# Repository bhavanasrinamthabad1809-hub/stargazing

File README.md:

#  Stargazing

**A panda-shaped task clock that nags me when it's time to start, yells when time's up, and gives me a star if I actually did the thing.**

## Why I made this

I am a professional procrastinator.

I don't mean "oh, I put things off a little." I mean I sit down to read a book for 30 minutes, and somehow it is two hours later and I have watched a video about how bridges are built. Phone alarms don't work on me, because I swipe them away without even waking up properly. To-do apps don't work either, because opening an app is already a task I'm avoiding.

So I asked myself: what if the thing that nags me was a *physical object* that sits on my desk, can't be swiped away, and is kind of cute so I don't hate it?

That's Stargazing. Every task has a **start time** and a **deadline**. At the start time it beeps at me. At the deadline it sounds an alarm. In between, I either press **DONE** and get a star in my little night sky, or I press **NOT DONE** and get nothing. It turns out I will do a surprising amount of work for a tiny pixel star.

---

## What it does

- Shows the **time and date** like a normal desk clock.
- Holds up to **10 tasks**, each with a name, a start time and a deadline.
- **Beeps at the start time** (three rising notes, repeated every minute until I press START).
- Shows a **countdown and a progress bar** while a task is running.
- Sounds a **siren at the deadline** until I press DONE or NOT DONE.
- Adds a **star to my star sky** for every task I finish, and the stars are saved even when it's unplugged.
- Lets me **add tasks from my phone** over Wi-Fi, with no app to install.
- Keeps the correct time even when the power is off, thanks to a battery-backed clock chip.
- Repeats my tasks every day, so I only have to type them in once.

**The three buttons** (left to right on the panda's belly): start not done done
Pressing `done` on the home screen shows my star sky.

---

## How it works 

1. I load my tasks from my phone 
2. The ESP32 keeps checking the time from the RTC.
3. When a task's start time arrives → **start alert**.
4. I press **START** → countdown begins.
5. When the deadline arrives → **siren**.
6. I press **DONE** ( +1) or **NOT DONE** (no star), and it moves on to the next task.

What if I ignore it?
- I never press START: after 10 minutes the task counts as **missed**.
- I ignore the siren: after 2 minutes it counts as **not done**.

(It really does not let me get away with anything. That's the point.)

###  pcb
schematic for my pcb 

pcb 

3d model of my pcb

## How the firmware works

The code is written in Arduino C++ 

**Main idea:**:

| State | What's happening | How it ends |
|---|---|---|
| WAITING | Home screen: time, date, next task | A task's start time arrives, or I press DONE to see the star sky |
| START_ALERT | Beeping, "TIME TO START" | I press START, or 10 minutes pass (missed) |
| RUNNING | Countdown and progress bar | Deadline arrives, or I press DONE / NOT DONE early |
| DEADLINE | Siren, "TIME'S UP!" | I press DONE or NOT DONE, or 2 minutes pass (not done) |
| RESULT | "GREAT JOB!" or "NOT DONE" for 3 seconds | Timer ends, back to `WAITING` |
| SKY | My stars | 5 seconds, or any button |

**cad time:**:
bottom case 

different view 

with pcb view

top case 

top view 

top back side view 

full box view 

**First time / changing tasks**
1. Unplug the clock, then plug it in **while holding START**.
2. On your phone, join the Wi-Fi **TaskClock** (password **panda1234**, you can change both in the code).
3. Open  in your browser.
4. Add your tasks (name, start, deadline) and press **Save to clock**.
5. It restarts by itself and you're done.

**Every day**
Just look at it. It will tell you what to do

## bill of materials 

| Component    | Quantity | Description         | Source                       | Price |
| ------------ | -------: | ------------------- | ---------------------------- | ----: |
| ESP32-C3 supermini    |        1 | Microcontroller     | [link](https://www.amazon.in/ESP32-Mini-Development-Board-Compatibility/dp/B0GQC8T6HV/ref=sr_1_8?crid=1YXDR902MUSIG&dib=eyJ2IjoiMSJ9.sGPT0TLrTVc4fjCA5M25kfKz9ewU1R1wIuoBckeM0x8HEPyzj9XwnklifiFo_89Bbb9mzE4WWo2DGeTRlLvV83Cb8s-klzuzTJVASNJNhv7Nqps-rZ-4lXOy6xMqxsJsVY7faohUpmPXMVEaXuAB03q0ysA6oRApeUPT93Cd3TyWsNSXOMPB1vQdJxj7mprZZuFzUoUwf0fJYcKTRnwLri9shof3BKq_yP47YysvE1c.27zLobKgGvnCgzQQ009P8C8V5wGSJ3_S2HBPNDYdVg8&dib_tag=se&keywords=esp32-c3+supermini&qid=1793557862&sprefix=esp32-c%2Caps%2C314&sr=8-8) | $8.21 |
| OLED Display |        1 | Small display       | [link](https://www.amazon.in/gp/product/B07Q7VZ716/ref=sw_img_1?smid=&psc=1) |$3.16 |
| 10K Resistor |        1 | Pull-up resistor    | [link](https://robocraze.com/products/10k-resistor-pack-of-10) | $1|
| switches  |        3 | User input buttons  | [link](https://www.amazon.in/gp/product/B0D9NGL25F/ref=ox_sc_act_title_6?smid=AJ6SIZC8YQDZX&psc=1) | $3.25 |
|  buzzer |        1 | alarm  | [link](https://robu.in/product/1-month-warranty-1248/) | $0.53 |
| PCB          |        1 | Custom-designed PCB | [link](https://jlcpcb.com/)  | $4|
| coin  battery | 1 | to work without the connection  | [Link](https://www.amazon.in/Microusb-Compatible-LIR2032-Rechargeable-Lithium/dp/B0DVCFHYPP/ref=pd_ci_mcx_mh_mcx_views_0_image?pd_rd_w=3fkGF&content-id=amzn1.sym.e8c4e9fa-b01e-4fcd-baf4-e39b1f74d04d%3Aamzn1.symc.30e3dbb4-8dd8-4bad-b7a1-a45bcdbc49b8&pf_rd_p=e8c4e9fa-b01e-4fcd-baf4-e39b1f74d04d&pf_rd_r=V9FM312QK4R5BZ1GMBEE&pd_rd_wg=6VyQf&pd_rd_r=a8b9df57-f77d-4994-88d4-a724bc4c2e68&pd_rd_i=B0DVCFHYPP) | $4.04 |
| rtc module | 1 | time tracking | [Link](https://robu.in/product/ds3231-rtc-module-precise-real-time-clock-i2c-at24c32/) | $1.32 |
| S8050 transistor | 1 | works as a switch to buzzer | [Link]() |  |
| 1k resistor | 1 | to work without the connection  | [Link]() |  |
| jumper wires | 1 | to solder with rtc  | [Link](https://robu.in/product/male-to-female-jumper-wires-40pcs-20cm/) | $0.53 |
| 1N4148 diode | 1 | to solder with rtc  | [Link](https://robu.in/product/1n4148-multicomp-pro-1n4148-diode-ultrafast-recovery-150ma-75v-do-204ah-2-2/) | $0.16 |
| m3screws | 1 | to solder with rtc  | [Link]() |  |
| pcb case | 1 | to place pcb  | [Link](https://robu.in/product/numaker-abs-filament-pure-white-1-75-mm-1-kg/) | $8.21  |

## Made with

KiCad, Onshape, , Arduino IDE, and a lot of avoiding my homework.

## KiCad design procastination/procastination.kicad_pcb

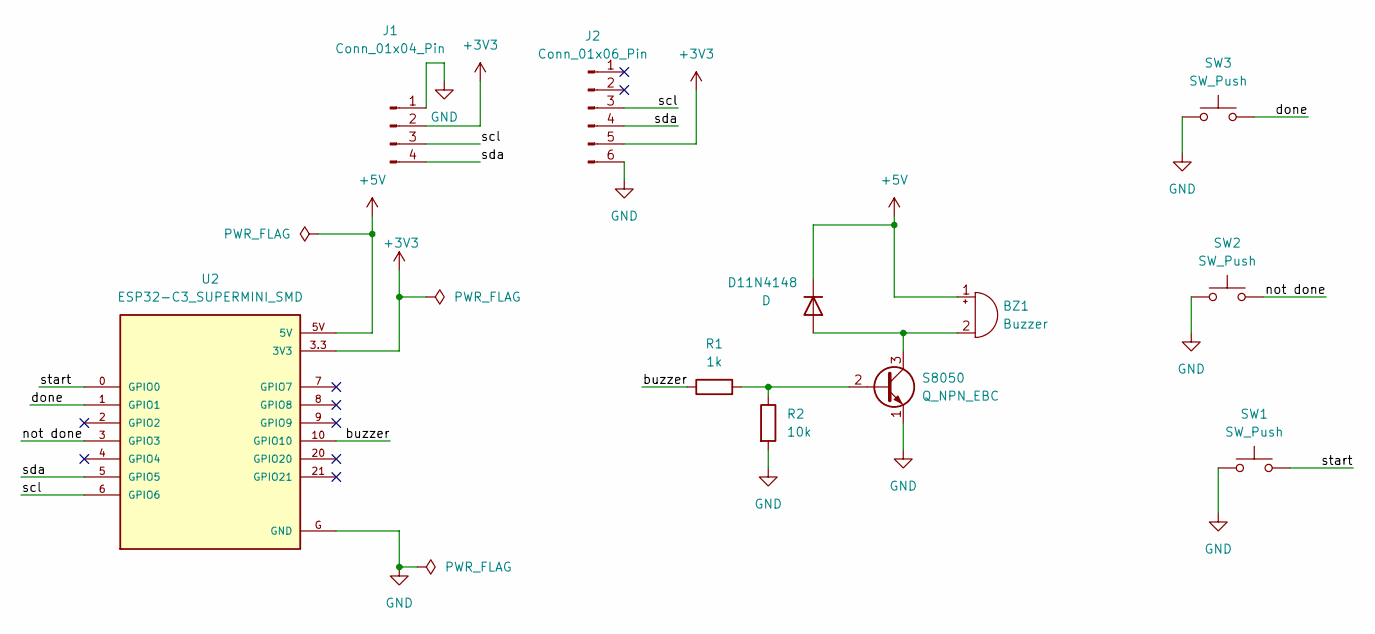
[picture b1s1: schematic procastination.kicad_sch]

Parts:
BZ1: Buzzer; Buzzer_12x9.5RM7.6
D11N4148: D; D_DO-35_SOD27_P7.62mm_Horizontal
J1: Conn_01x04_Pin; Display_128x64_096_I2C
J2: Conn_01x06_Pin; PinSocket_1x06_P2.54mm_Vertical
R1: 1k; R_Axial_DIN0207_L6.3mm_D2.5mm_P10.16mm_Horizontal
R2: 10k; R_Axial_DIN0207_L6.3mm_D2.5mm_P10.16mm_Horizontal
S8050: Q_NPN_EBC; TO-92_Inline
SW1, SW2, SW3: SW_Push; SW_PUSH-12mm
U2: ESP32-C3_SUPERMINI_SMD; MODULE_ESP32-C3_SUPERMINI

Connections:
+3V3: J1.2, J2.5, U2.3.3 (3V3)
+5V: BZ1.1 (+), D11N4148.1 (K), U2.5V
/buzzer: R1.1, U2.10 (GPIO10)
/done: SW3.2, U2.1 (GPIO1)
/not done: SW2.2, U2.3 (GPIO3)
/scl: J1.3, J2.3, U2.6 (GPIO6)
/sda: J1.4, J2.4, U2.5 (GPIO5)
/start: SW1.2, U2.0 (GPIO0)
GND: J1.1, J2.6, R2.2, S8050.1 (E), SW1.1, SW2.1, SW3.1, U2.G (GND)
unnamed: BZ1.2 (-), D11N4148.2 (A), S8050.3 (C)
unnamed: R1.2, R2.1, S8050.2 (B)

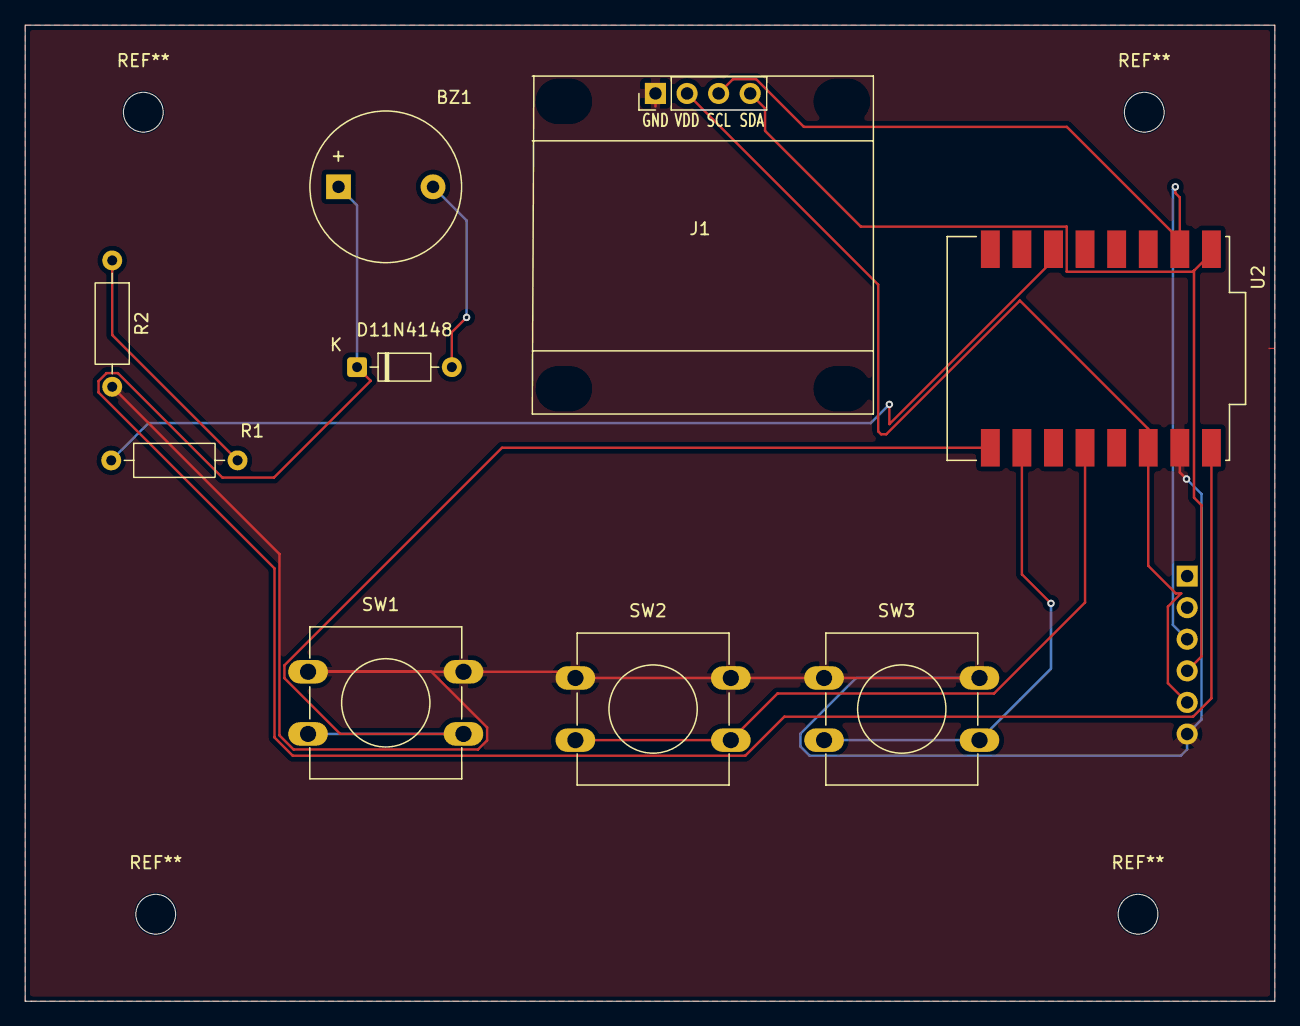
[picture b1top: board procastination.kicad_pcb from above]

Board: 2 copper layers, 100.5 x 78.5 mm, 10 parts (1 on the bottom side), 11 nets.
